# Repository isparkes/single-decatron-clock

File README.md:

# Single Decatron Clock Firmware

Firmware for a clock built around a single Decatron (Dekatron) cold-cathode
gas-discharge tube — a 1950s-era 30-position counting tube repurposed here as
an analogue-style hours/minutes/seconds display.

Current software version: `4`

See [`SPECIFICATION.md`](SPECIFICATION.md) for the full hardware/firmware
specification and [`DecatronClockFirmware/USER_MANUAL.md`](DecatronClockFirmware/USER_MANUAL.md)
for end-user documentation of the web interface and configuration options.

## Hardware overview

An ESP8266 (Wemos D1 Mini) drives a Decatron tube through a two-guide
stepping scheme, decoding a rotary glow position from three interrupt phases
per step (30 pin-steps per revolution). The device runs as either a
standalone clock (NTP with DS1307 RTC fallback) or as an I2C slave to a
master clock — in this repo's current configuration, an
[ENIAC Nixie clock](../eniac-firmware) — which pushes wall-clock time and
blanking state once per second.

## Highlights

Some of the more interesting problems this firmware solves:

- **Single-interrupt display multiplexing with per-dot brightness weighting**
  — one `timer1` ISR steps the tube through all 30 positions, comparing the
  current pin against three independently tracked display targets
  (hours/minutes/seconds) and re-arming itself with a dwell count scaled 60×,
  15×, or 5× the base "off" duration. Three dots glow simultaneously at
  three distinct brightness levels from a single timer, with no separate
  PWM channel per dot.
- **Self-homing via a swappable ISR** — at boot the firmware runs a slow
  *scanning* interrupt handler that free-runs the tube until a physical index
  sense pin fires, then hot-swaps `timer1`'s callback to the normal *display*
  handler. The index trigger continues correcting drift at every revolution,
  so the tube's absolute glow position never has to be assumed — it's always
  physically re-derived.
- **Graceful multi-source time arbitration** — an I2C slave callback
  (`ICACHE_RAM_ATTR`, interrupt-context, exactly 4 bytes, no blocking) accepts
  push updates from a master clock once per second and overrides local state;
  if a second passes with no packet, the display falls back to its own
  NTP-derived clock and locally computed blanking without a hiccup. All the
  actual decision logic runs in the main loop — the ISR only stashes bytes
  into `volatile` buffers.
- **Layered blanking with escalating button override** — day/week schedule,
  PIR motion timeout, and an explicit remote "blanked" command from the I2C
  master all compete to blank the tube, and a single button independently
  suppresses all of them: press once to hold the display on for a minute,
  twice in quick succession for an hour, three times for a day, with the
  press count decoded from timing between presses.
- **Perceptually-tuned spin-up ramp** — coming out of blanking, the HV supply
  re-enables and the multiplex dwell count ramps back down from a 250,000-count
  "off" dwell to a 1,000-count "on" dwell at one of three configurable rates,
  so the tube visibly fades in rather than snapping to full brightness.
- **Self-describing status page** — the root web page live-scans all 128 I2C
  addresses to report connected peripherals, and encodes overall device
  health (WiFi / NTP / SPIFFS / OTA-available / auth / debug) as a compact
  single-character status string, alongside uptime and tube-on-time
  statistics persisted to SPIFFS.
- **Zero-touch provisioning and recovery** — first boot (or a factory reset
  triggered by holding the button at power-up) opens a WiFiManager captive
  portal; once configured, the device is reachable by mDNS hostname, supports
  OTA updates gated on available flash headroom, and independently exposes
  WiFi-only, config-only, and full-factory reset endpoints.

## Repository layout

| Path | Description |
|---|---|
| [`DecatronClockFirmware`](DecatronClockFirmware) | Main Arduino sketch and supporting modules (display ISR, I2C slave, web server, NTP, RTC, SPIFFS config, button handling, debug logging). |
| [`decatron_clock_test`](decatron_clock_test) | Standalone bench sketch for exercising the Decatron tube stepping logic in isolation. |

## Building

This is an Arduino sketch targeting the ESP8266 core.

```bash
# Board: Lolin/Wemos D1 Mini, 160 MHz, Flash 4MB (FS: 2MB, OTA: ~1MB)
# Open DecatronClockFirmware/DecatronClockFirmware.ino in the Arduino IDE
# or build with arduino-cli:
arduino-cli compile --fqbn esp8266:esp8266:d1_mini DecatronClockFirmware
arduino-cli upload  --fqbn esp8266:esp8266:d1_mini -p <port> DecatronClockFirmware
```

Dependencies: [`TimeLib`](https://github.com/michaelmargolis/arduino_time),
[`WiFiManager`](https://github.com/tzapu/WiFiManager), and the ESP8266
Arduino core (`ESP8266WiFi`, `ESP8266WebServer`, `ESP8266HTTPUpdateServer`,
`ESP8266mDNS`, `LittleFS`/`SPIFFS`, `Wire`).

## Documentation

- [`SPECIFICATION.md`](SPECIFICATION.md) — full hardware/firmware specification, including the I2C protocol, GPIO map, and configuration parameters
- [`DecatronClockFirmware/USER_MANUAL.md`](DecatronClockFirmware/USER_MANUAL.md) / [`USER_MANUAL.html`](DecatronClockFirmware/USER_MANUAL.html) — end-user manual

## License

This project is licensed under a strict Attribution-NonCommercial license — see
[`LICENSE`](LICENSE) for the full text. In short: attribution to Ian Sparkes is required, and
commercial use is not permitted without a separate written license.

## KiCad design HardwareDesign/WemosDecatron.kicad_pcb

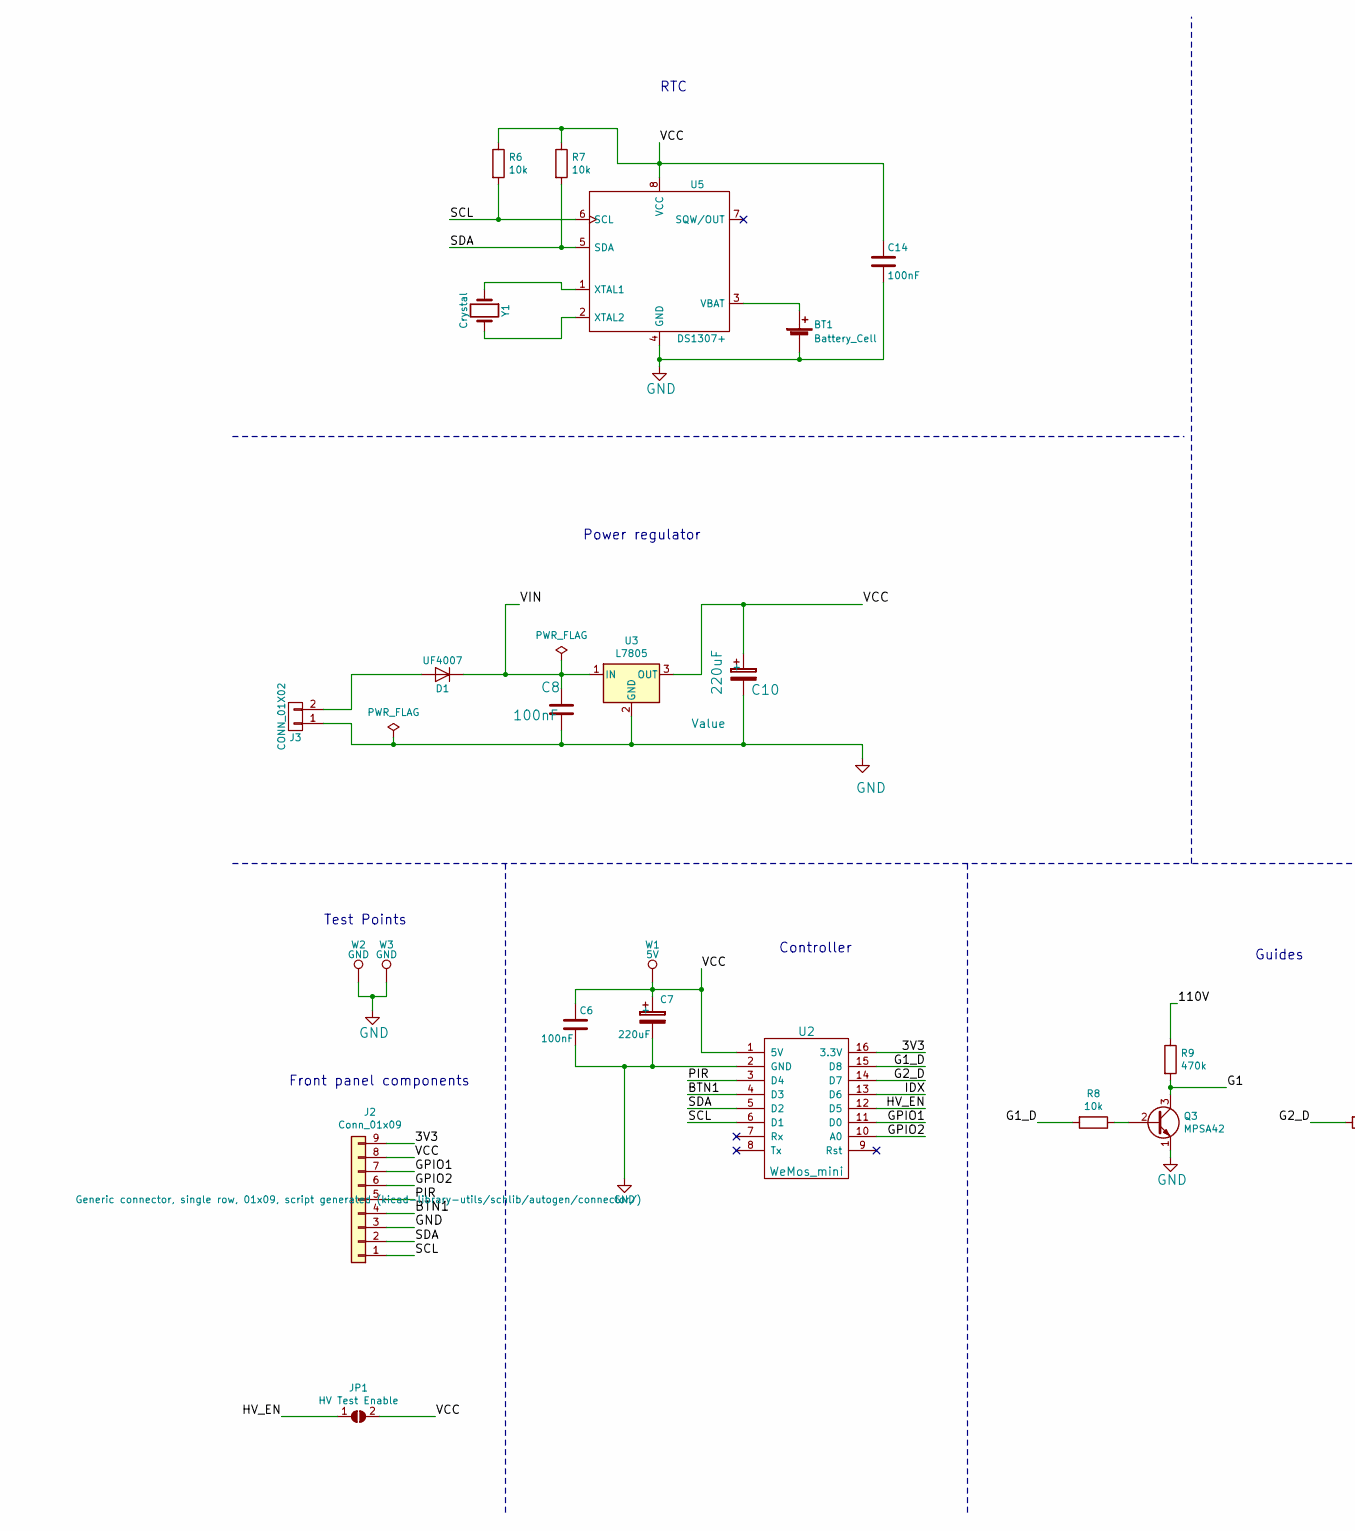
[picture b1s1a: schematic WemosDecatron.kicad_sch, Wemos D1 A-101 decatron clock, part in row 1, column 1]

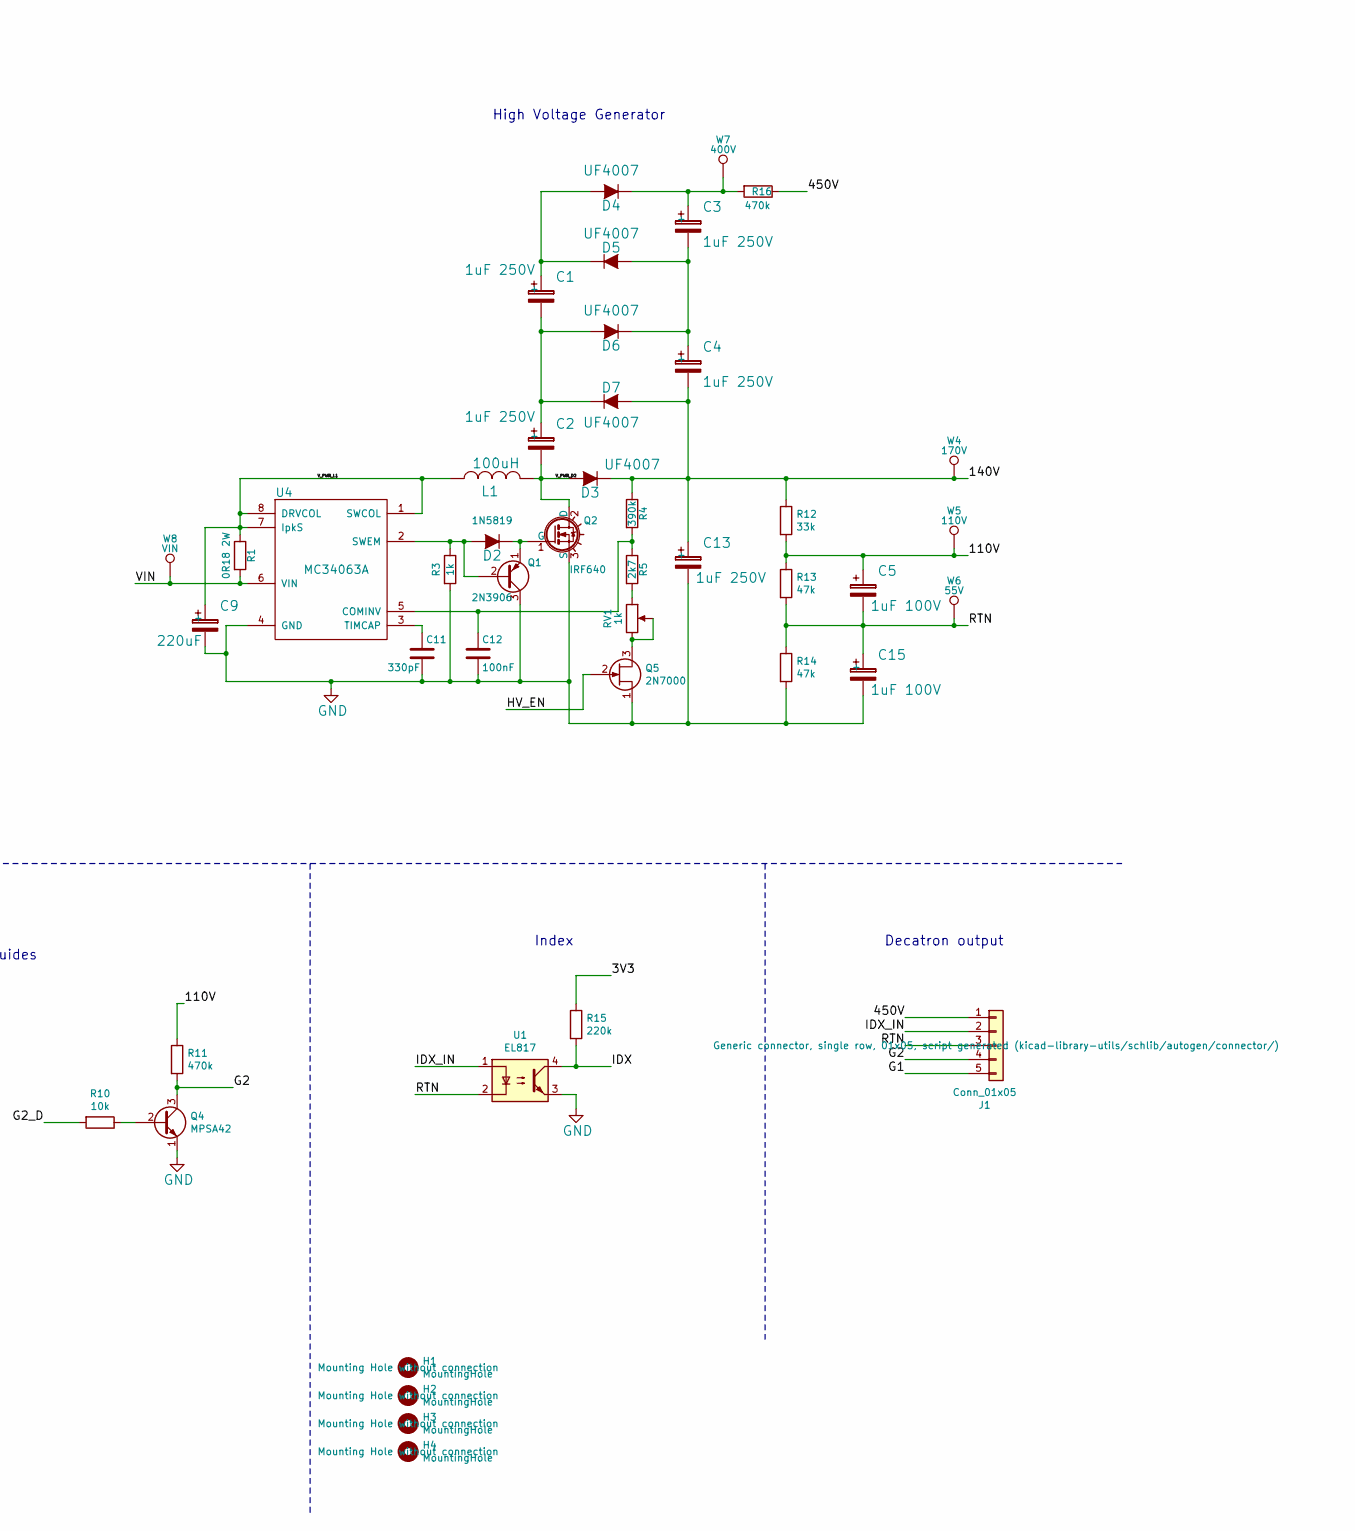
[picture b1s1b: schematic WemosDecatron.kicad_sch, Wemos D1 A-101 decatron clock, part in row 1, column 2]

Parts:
BT1: Battery_Cell; CR1220-CoinCell
C1, C2, C3, C4, C13: 1uF 250V; CP_Radial_D5.0mm_P2.50mm
C5, C15: 1uF 100V; CP_Radial_D5.0mm_P2.50mm
C6, C8, C12, C14: 100nF; C025-024X044
C7, C9, C10: 220uF; C_Radial_D6.3_L11.2_P2.5
C11: 330pF; C025-024X044
D1: UF4007; Diode_DO-41_SOD81_Vertical_AnodeUp
D2: 1N5819; Diode_DO-41_SOD81_Vertical_AnodeUp
D3, D4, D5, D6, D7: UF4007; Diode_DO-41_1N4001
H1, H2, H3, H4: MountingHole; MountingHole_3.2mm_M3
J1: Conn_01x05; Header_MA05-1
J2: Conn_01x09; Header_MA09-1
J3: CONN_01X02; Header_MA02-1
JP1: HV Test Enable; SOLDER-JUMPER
L1: 100uH; Inductor-100mH
Q1: 2N3906; TO-92_inline_2N3906
Q2: IRF640; TO-220-3_H
Q3, Q4: MPSA42; TO-92_inline_MPSA42
Q5: 2N7000; TO-92_inline_2N7000
R1: 0R18 2W; R_2W
R3: 1k; R-0207_2V
R4: 390k; R-0207_2V
R5: 2k7; R-0207_2V
R6, R7, R8, R10: 10k; R-0207_2V
R9, R11, R16: 470k; R-0207_2V
R12: 33k; R-0207_2V
R13, R14: 47k; R-0207_2V
R15: 220k; R-0207_2V
RV1: 1k; Potentiometer_Trimmer_Bourns_3296X
U1: EL817; optocoupler-DIL04
U2: WeMos_mini; WeMos_D1_mini_board_flipped
U3: L7805; TO-220-3_H
U4: MC34063A; MC34063_DIL8
U5: DS1307+; DS1307_DIL8
W1: 5V; TESTPAD_P1-13
W2, W3: GND; TESTPAD_P1-13
W4: 170V; TESTPAD_P1-13
W5: 110V; TESTPAD_P1-13
W6: 55V; TESTPAD_P1-13
W7: 400V; TESTPAD_P1-13
W8: VIN; TESTPAD_P1-13
Y1: Crystal; Crystal_DS10_d1.0mm_l4.3mm_Vertical

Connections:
/3V3: J2.9, R15.1, U2.16 (3.3V)
/110V: C5.1, R9.1, R11.1, R12.2, R13.1, W5.1
/140V: C4.2, C13.1, D3.1 (K), D7.2 (A), R4.1, R12.1, W4.1
/450V: J1.1, R16.1
/BTN1: J2.4, U2.4 (D3)
/G1: J1.5, Q3.3 (C), R9.2
/G1_D: R8.2, U2.15 (D8)
/G2: J1.4, Q4.3 (C), R11.2
/G2_D: R10.2, U2.14 (D7)
/GPIO1: J2.7, U2.11 (D0)
/GPIO2: J2.6, U2.10 (A0)
/HV_EN: JP1.1 (A), Q5.2 (G), U2.12 (D5)
/IDX: R15.2, U1.4, U2.13 (D6)
/IDX_IN: J1.2, U1.1
/PIR: J2.5, U2.3 (D4)
/RTN: C5.2, C15.1, J1.3, R13.2, R14.1, U1.2, W6.1
/SCL: J2.1, R6.2, U2.6 (D1), U5.6 (SCL)
/SDA: J2.2, R7.2, U2.5 (D2), U5.5 (SDA)
/VCC: C6.1, C7.1, C10.1, C14.1, J2.8, JP1.2 (B), R6.1, R7.1, U2.1 (5V), U3.3 (OUT), U5.8 (VCC), W1.1
/VIN: C8.2, D1.1 (K), R1.2, U3.1 (IN), U4.6 (VIN), W8.1
/V_PWR_D2: C2.2, D3.2 (A), L1.2, Q2.2 (D)
/V_PWR_L1: C9.1, L1.1, R1.1, U4.1 (SWCOL), U4.7 (IpkS), U4.8 (DRVCOL)
GND: BT1.2 (-), C6.2, C7.2, C8.1, C9.2, C10.2, C11.2, C12.2, C13.2, C14.2, C15.2, J2.3, J3.1, Q1.3 (C), Q2.3 (S), Q3.1 (E), Q4.1 (E), Q5.1 (S), R3.2, R14.2, U1.3, U2.2 (GND), U3.2 (GND), U4.4 (GND), U5.4 (GND), W2.1, W3.1
unnamed: BT1.1 (+), U5.3 (VBAT)
unnamed: D1.2 (A), J3.2
unnamed: D2.2 (A), Q1.2 (B), R3.1, U4.2 (SWEM)
unnamed: D2.1 (K), Q1.1 (E), Q2.1 (G)
unnamed: C1.1, D4.2 (A), D5.1 (K)
unnamed: C3.1, D4.1 (K), R16.2, W7.1
unnamed: C3.2, C4.1, D5.2 (A), D6.1 (K)
unnamed: C1.2, C2.1, D6.2 (A), D7.1 (K)
unnamed: Q3.2 (B), R8.1
unnamed: Q4.2 (B), R10.1
unnamed: Q5.3 (D), RV1.2, RV1.3
unnamed: R5.2, RV1.1
unnamed: C12.1, R4.2, R5.1, U4.5 (COMINV)
unnamed: C11.1, U4.3 (TIMCAP)
unnamed: U5.1 (XTAL1), Y1.1
unnamed: U5.2 (XTAL2), Y1.2

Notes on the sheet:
Power regulator
Index
Controller
Front panel components
RTC
Decatron output
High Voltage Generator
Guides
Test Points

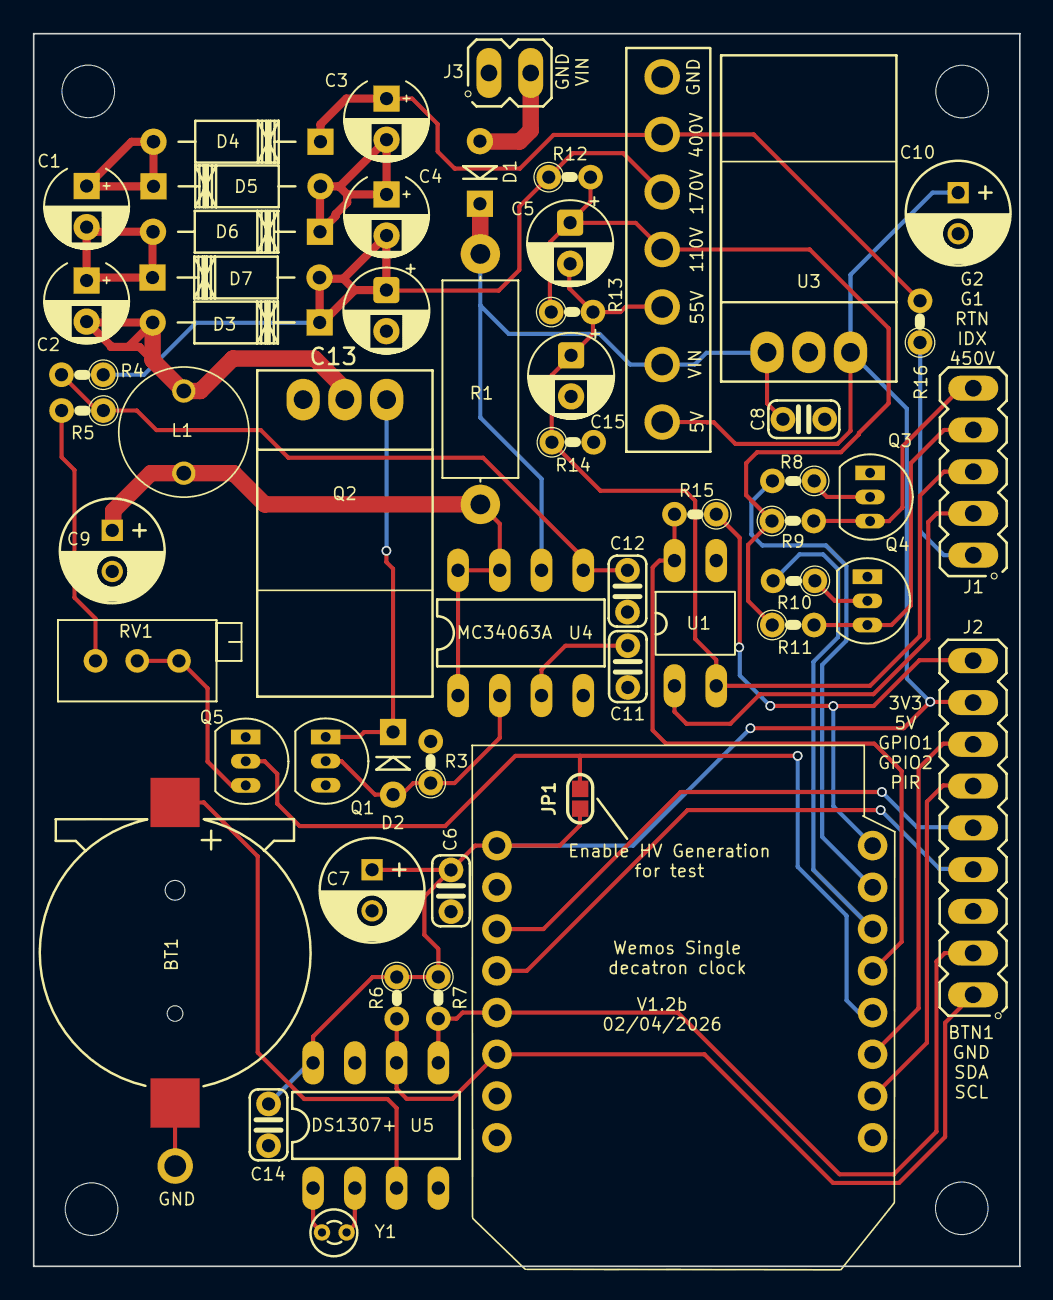
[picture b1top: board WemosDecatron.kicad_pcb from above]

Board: 2 copper layers, 60.0 x 75.0 mm, 67 parts (0 on the bottom side), 39 nets.

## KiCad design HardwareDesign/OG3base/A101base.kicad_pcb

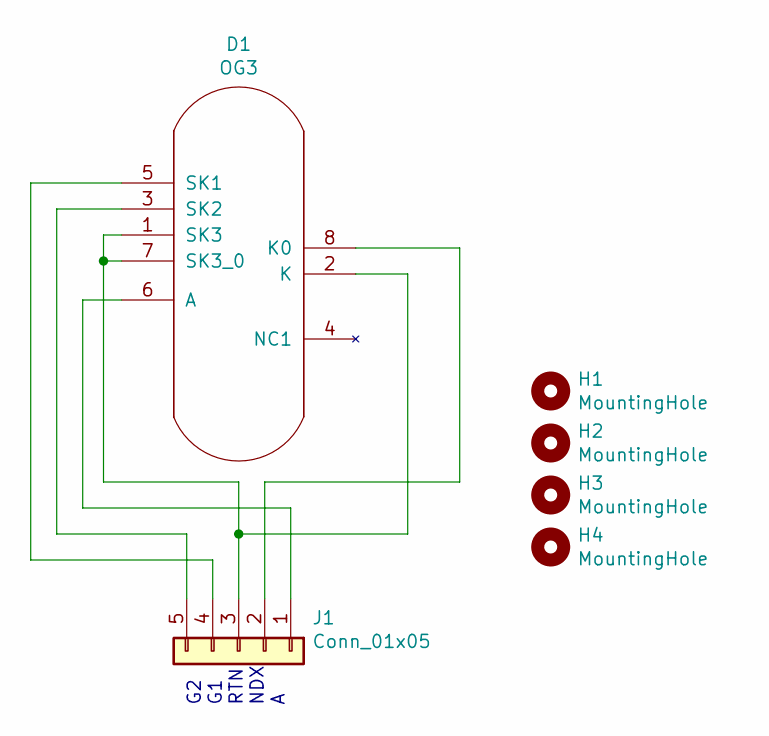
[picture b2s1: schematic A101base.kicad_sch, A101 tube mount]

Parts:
D1: OG3; OG4
H1, H2, H3, H4: MountingHole; MountingHole_3.2mm_M3
J1: Conn_01x05; Header_MA05-1

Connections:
unnamed: D1.1 (SK3), D1.2 (K), D1.7 (SK3_0), J1.3
unnamed: D1.3 (SK2), J1.5
unnamed: D1.5 (SK1), J1.4
unnamed: D1.6 (A), J1.1
unnamed: D1.8 (K0), J1.2

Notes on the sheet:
G2 G1 RTN NDX A

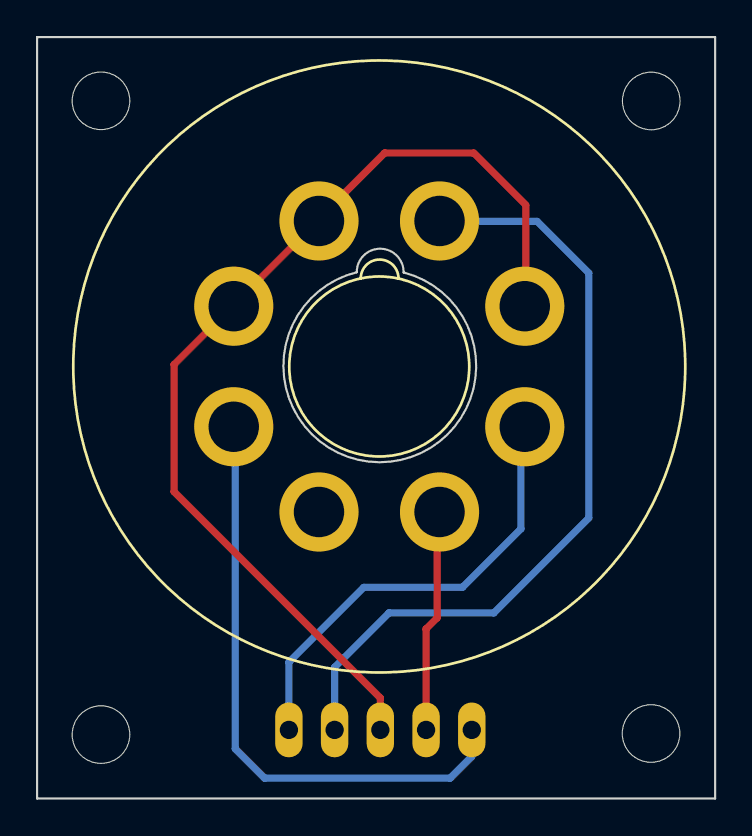
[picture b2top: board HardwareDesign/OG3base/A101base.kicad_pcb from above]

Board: 2 copper layers, 37.7 x 42.3 mm, 6 parts (1 on the bottom side), 5 nets.

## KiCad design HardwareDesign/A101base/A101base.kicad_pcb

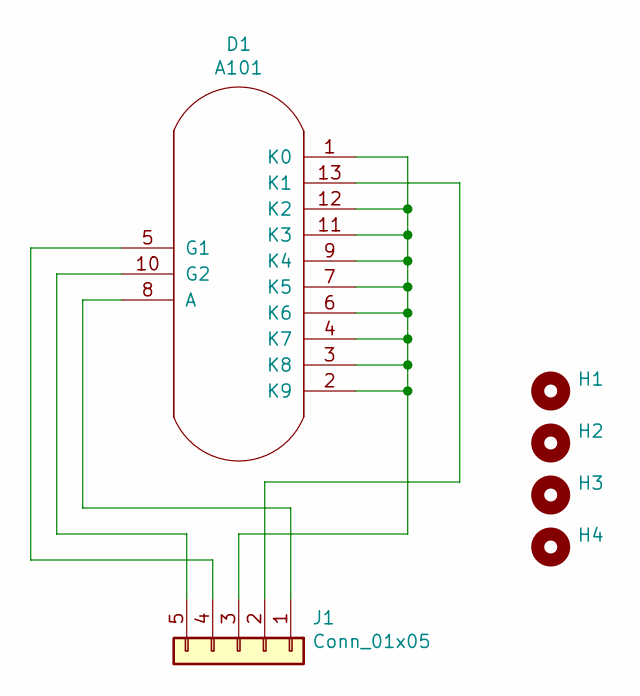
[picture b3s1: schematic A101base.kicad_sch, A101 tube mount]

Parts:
D1: A101; A101-TopView
H1, H2, H3, H4: MountingHole; MountingHole_3.2mm_M3
J1: Conn_01x05; Header_MA05-1

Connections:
unnamed: D1.1 (K0), D1.2 (K9), D1.3 (K8), D1.4 (K7), D1.6 (K6), D1.7 (K5), D1.9 (K4), D1.11 (K3), D1.12 (K2), J1.3
unnamed: D1.5 (G1), J1.4
unnamed: D1.8 (A), J1.1
unnamed: D1.10 (G2), J1.5
unnamed: D1.13 (K1), J1.2

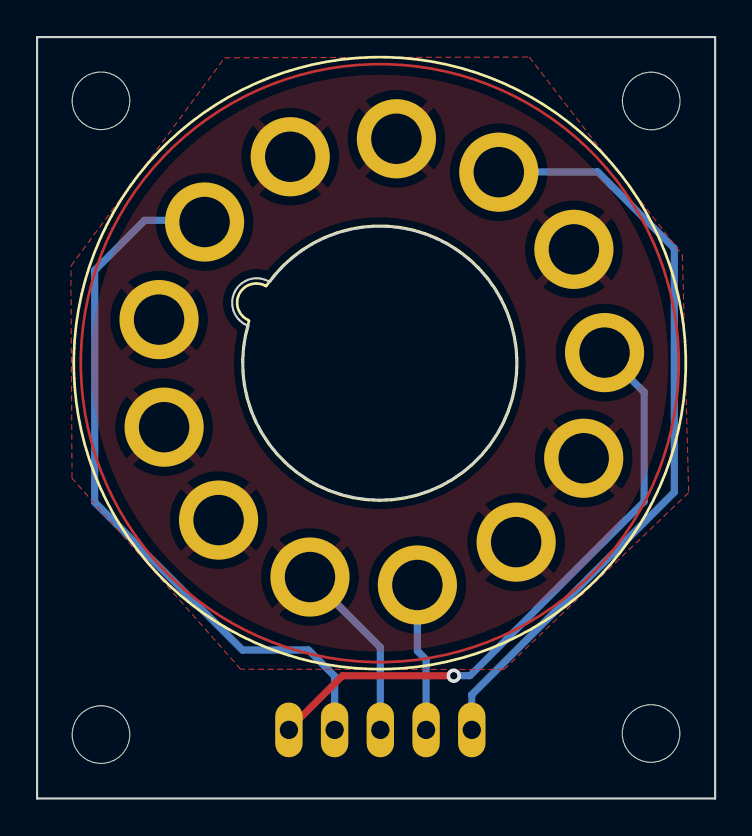
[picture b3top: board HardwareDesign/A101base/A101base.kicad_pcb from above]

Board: 2 copper layers, 37.7 x 42.3 mm, 6 parts (1 on the bottom side), 5 nets.

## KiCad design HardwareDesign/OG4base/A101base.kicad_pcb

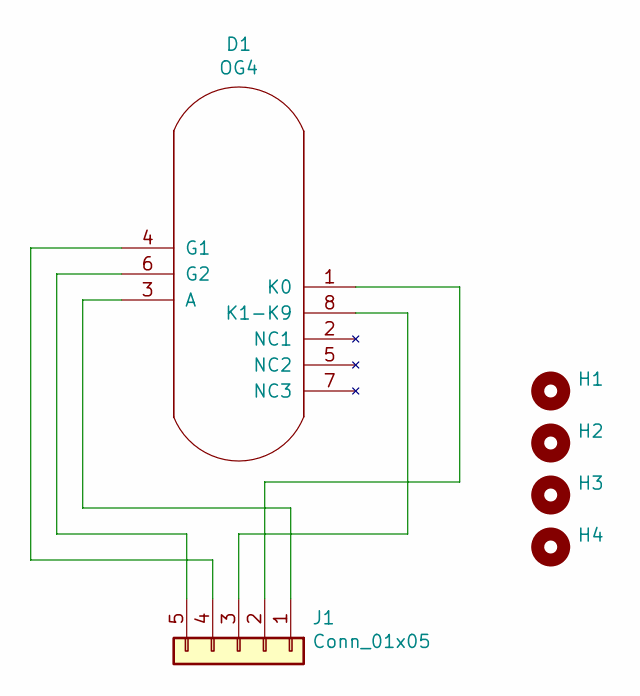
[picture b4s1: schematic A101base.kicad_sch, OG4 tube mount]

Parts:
D1: OG4
H1, H2, H3, H4: MountingHole; MountingHole_3.2mm_M3
J1: Conn_01x05; Header_MA05-1

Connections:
unnamed: D1.1 (K0), J1.2
unnamed: D1.3 (A), J1.1
unnamed: D1.4 (G1), J1.4
unnamed: D1.6 (G2), J1.5
unnamed: D1.8 (K1-K9), J1.3

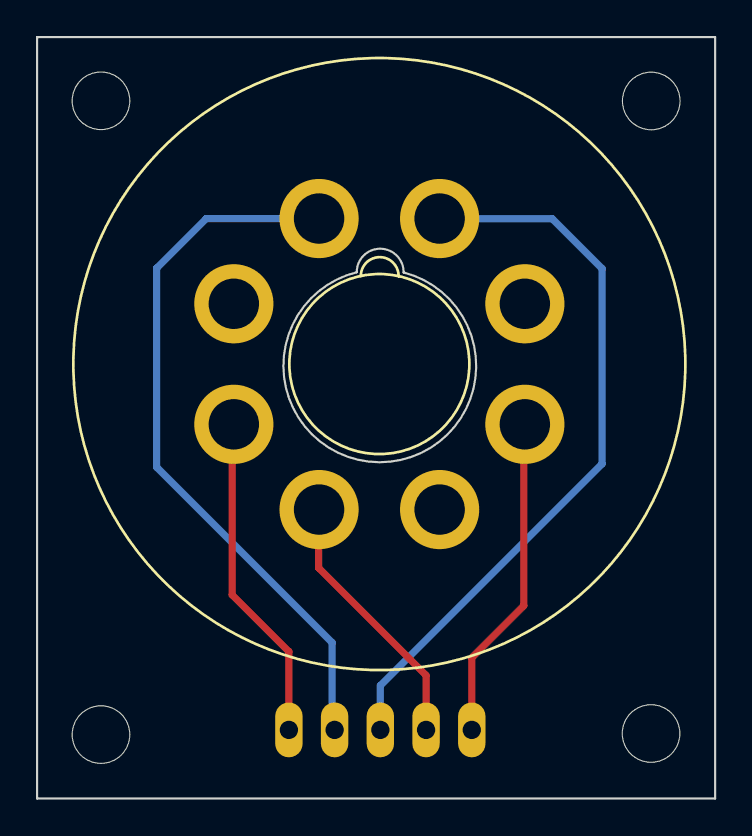
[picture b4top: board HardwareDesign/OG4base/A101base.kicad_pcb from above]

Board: 2 copper layers, 37.7 x 42.3 mm, 6 parts (1 on the bottom side), 5 nets.
